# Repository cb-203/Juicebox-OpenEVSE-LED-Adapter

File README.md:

# JuiceBox-OpenEVSE LED Adapter

This printed circuit board design adapts the 
[OpenEVSE v1 JuiceBox replacement board](https://store.openevse.com/collections/all-products/products/replacement-electronics-for-juicebox-v1-metal-black-and-orange)'s 
LED connector to work with the LED harnesses in later model eMotorWerks JuiceBox units.

Prior to the redesign and release of the "v2" JuiceBox model following the acquisition of 
eMotorWerks by EnelX in late 2017, many (most?) "v1" JuiceBox units were provided 
with LED harnesses requiring +5V power to each LED with a common ground return path (+ + + -). 
However, earlier models of the v1 design included harnesses having the opposite polarity (- - - +).

The first implementations of the OpenEVSE replacement board were designed around the 
earlier model JuiceBoxes with the (- - - +) orientation and were quickly found to be incompatible 
with the later model JuiceBox LED harnesses.  Due to the way the LED harnesses were installed into 
the cover of the JuiceBox unit, reorienting or replacing the LEDs was considered impractical. 
Although OpenEVSE have since developed a common ground variant of the replacement board, 
this project aims to bridge the gap between the earlier model OpenEVSE boards and later model 
JuiceBox LED harnesses by translating the voltages from one orientation to the other using a small 
adapter board.

Files in this project are implemented in [KiCad](https://www.kicad.org) version 8.0.

$${\color{white}.}$$

## Board Layout and Components

* J1, J2: 4-pin FFC connector, vertical, 1.0 mm pitch
* R1, R2: 2.4 kOhm resistor, 0603 package
* R3: 75 Ohm resistor, 0603 package
* Q1: Dual PNP/PNP transistors, SOT-363 package
* F1: Flat Flexible Cable (FFC), 4-pin, 1.0 mm pitch, 10 cm length, same-side, insert into J1

$${\color{white}.}$$

## The Schematic

As shown in the schematic diagram, the PWR pin on the OpenEVSE board (J1, pin 4) is used as the 
source of common ground for the LEDs.  Since the power light is always on, it is presumed that 
this pin will never be switched off while the other LEDs are in use.  Therefore, power from the 
+5V pin 1 is routed directly to the LED harness's green power LED (J2, pin 1), and the PWR pin 
(now treated as the source for ground) is routed to the harness's common ground (J2, pin 4).

The other two LEDs are switched on ground.  When the LEDs are off, the WIFI and/or CHG pins on 
the OpenEVSE board are floating.  When on, these pins are connected to ground.  To convert this 
behavior into +5V power for each LED, a pair of PNP transistors is used.  +5V is routed to the 
emitter of each transistor, and the collector is connected to each corresponding LED.  When 
negative voltage is applied to the base of each transistor via the WIFI and CHG pins on the 
controller board, the transistor is opened allowing +5V current to flow through to the LED, 
returning on the common ground lane.

Resistors are used on each transistor's base pin to limit the current draw from the emitter 
through the base.  An additional resistor is also added to the red CHG LED to reduce its 
current draw.  Through experimentation, without the added resistance, this LED was found to pull 
about 22 mA of current, while the green and blue LEDs pull closer to 13 mA.  Even with the added 
resistance, the red LED subjectively appears to provide very similar brightness to the other 
two lights.

$${\color{white}.}$$

## Current flow

Simulating the circuit with proposed resistor values using the 
[Falstad Circuit Simulator](https://www.falstad.com), 
this diagram shows the approximate current at each section of the circuit.  At worst case, 
the board is expected to pull no more than 45 to 50 mA. 

The resistors shown adjacent to the LEDs are included in the existing LED harness. 
In the simulation, the values for these resistors were set to approximate the current 
measured at each LED.  As noted above, the red LED was found to pull about 22 mA without 
additional resistance, while the green and blue LEDs each pull about 13 mA.

$${\color{white}.}$$

$${\color{white}.}$$

$${\color{white}.}$$

$${\color{white}.}$$

$${\color{white}.}$$

$${\color{white}.}$$

$${\color{white}.}$$

## Prototype

Proof-of-concept prototype boards fabricated in March 2025 using [JLCPCB.com](https://jlcpcb.com) 
board manufacture with component assembly:

Adapter installed into a JuiceBox Pro 32 with OpenEVSE v1 replacement board.  The adapter is 
affixed to the side wall of the JuiceBox enclosure with foam mounting tape.

All lights are on for a few seconds when the device is first powered on.  When ready, only the 
green LED is illuminated.  While charging, the red LED is also lit.  The blue LED is used to 
indicate an error state (not pictured) but will also momentarily light up when the unit is 
powered off (also not pictured).

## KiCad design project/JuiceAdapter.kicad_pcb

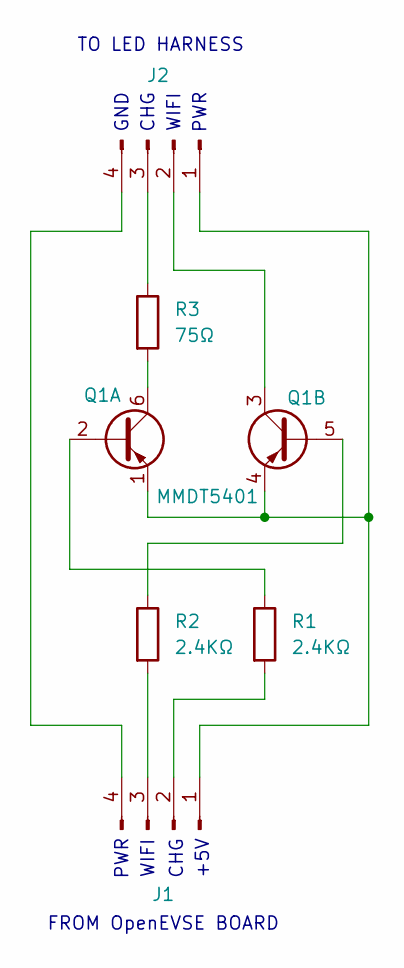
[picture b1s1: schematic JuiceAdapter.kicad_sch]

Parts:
J1, J2: Conn_01x04_Pin; STWXE FC38-04N0-AHS; LCSC PN C7499262
Q1: MMDT5401; SOT-363_SC-70-6; LCSC PN C968396
R1, R2: 2.4KΩ; R_0603_1608Metric; LCSC PN C22940
R3: 75Ω; R_0603_1608Metric; LCSC PN C4275

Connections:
unnamed: J1.1, J2.1, Q1.1 (E1), Q1.4 (E2)
unnamed: J1.2, R1.2
unnamed: J1.3, R2.2
unnamed: J1.4, J2.4
unnamed: J2.2, Q1.3 (C2)
unnamed: J2.3, R3.1
unnamed: Q1.2 (B1), R1.1
unnamed: Q1.6 (C1), R3.2
unnamed: Q1.5 (B2), R2.1

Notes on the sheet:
PWR
GND
TO LED HARNESS
FROM OpenEVSE BOARD
+5V
WIFI
CHG

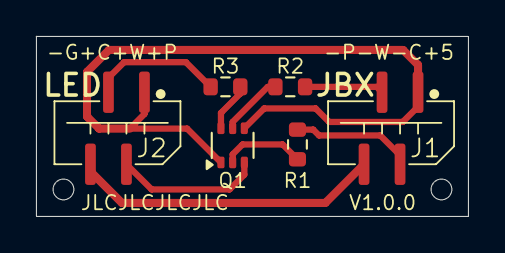
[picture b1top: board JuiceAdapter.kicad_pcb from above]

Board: 2 copper layers, 24.0 x 10.0 mm, 6 parts (0 on the bottom side), 9 nets.

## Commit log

2025-03-23 Clarified resistor values on schematic and PCB.
2025-03-23 Add narrative and images to README.
2025-03-23 Updated schematic size and rendering background on README.
2025-03-23 Update rendering.
2025-03-25 Clarified project organization, updated README
2025-03-25 Corrected image reference in README
2025-03-25 Corrected image size in README
2025-03-25 Clarified README
2025-03-25 Enhanced README
2025-03-26 Paragraph spacing in README
2025-03-26 Relocated drill and placement origin
2025-03-27 Adjusted traces for single-sided board
2025-03-28 Improved rendering image
2025-05-18 Add board layout to documentation
